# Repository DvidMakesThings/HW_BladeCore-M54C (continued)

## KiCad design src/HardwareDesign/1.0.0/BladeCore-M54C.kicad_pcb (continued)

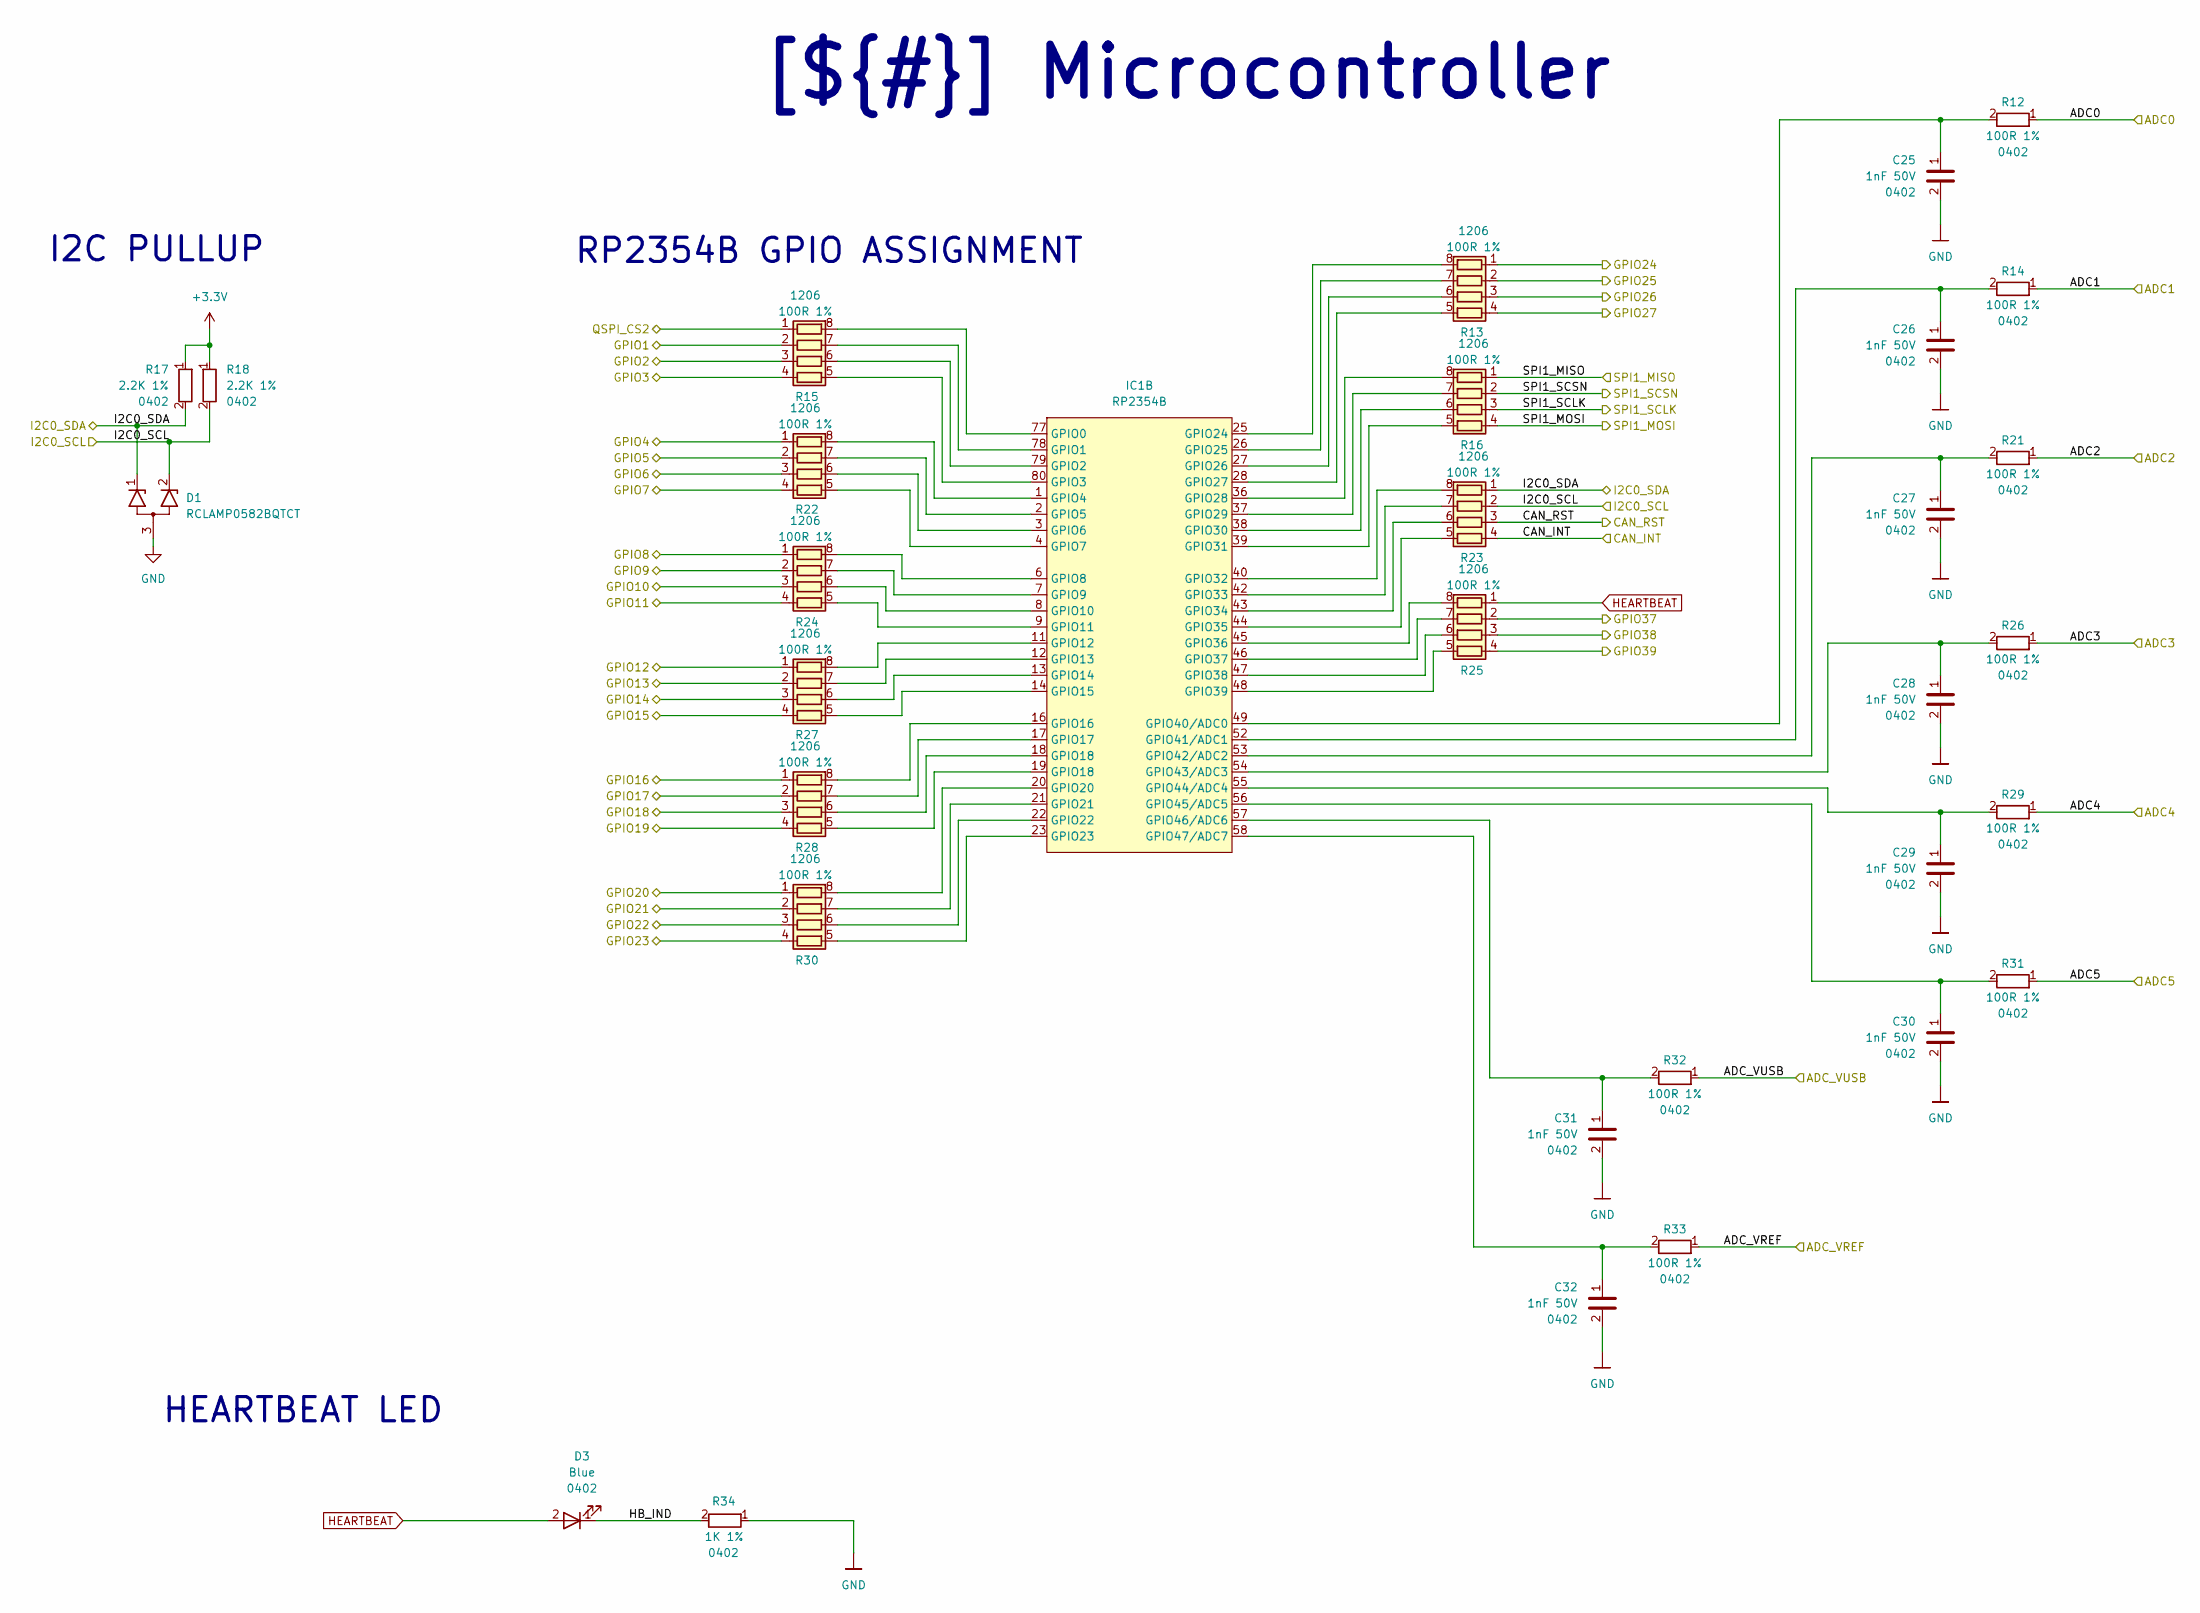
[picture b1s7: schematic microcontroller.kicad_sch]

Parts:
C25, C26, C27, C28, C29, C30, C31, C32: 1nF 50V; C_0402_1005Metric; LCSC_PART C14442
D1: RCLAMP0582BQTCT; SOT-416; MPN RCLAMP0582BQTCT; LCSC_PART C841193
D3: Blue; LED_0402_1005Metric; MPN XL-1005UBC; LCSC_PART C22355736
IC1: RP2354B; QFN80_10x10; MPN RP2354B; LCSC_PART C39843328
R12, R14, R21, R26, R29, R31, R32, R33: 100R 1%; R_0402_1005Metric; LCSC_PART C25076
R13, R15, R16, R22, R23, R24, R25, R27, R28, R30: 100R 1%; R_Array_Convex_4x0603; MPN YC164-FR-07100RL; LCSC_PART C136838
R17, R18: 2.2K 1%; R_0402_1005Metric; LCSC_PART C25879
R34: 1K 1%; R_0402_1005Metric; LCSC_PART C11702

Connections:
+3.3V: R17.1, R18.1; also elsewhere on the board
/Project Architecture/ADC0: R12.1; also elsewhere on the board
/Project Architecture/ADC1: R14.1; also elsewhere on the board
/Project Architecture/ADC2: R21.1; also elsewhere on the board
/Project Architecture/ADC3: R26.1; also elsewhere on the board
/Project Architecture/ADC4: R29.1; also elsewhere on the board
/Project Architecture/ADC5: R31.1; also elsewhere on the board
/Project Architecture/GPIO0: R15.1 (R11); also elsewhere on the board
/Project Architecture/GPIO1: R15.2 (R12); also elsewhere on the board
/Project Architecture/GPIO2: R15.3 (R13); also elsewhere on the board
/Project Architecture/GPIO3: R15.4 (R14); also elsewhere on the board
/Project Architecture/GPIO4: R22.1 (R11); also elsewhere on the board
/Project Architecture/GPIO5: R22.2 (R12); also elsewhere on the board
/Project Architecture/GPIO6: R22.3 (R13); also elsewhere on the board
/Project Architecture/GPIO7: R22.4 (R14); also elsewhere on the board
/Project Architecture/GPIO8: R24.1 (R11); also elsewhere on the board
/Project Architecture/GPIO9: R24.2 (R12); also elsewhere on the board
/Project Architecture/GPIO10: R24.3 (R13); also elsewhere on the board
/Project Architecture/GPIO11: R24.4 (R14); also elsewhere on the board
/Project Architecture/GPIO12: R27.1 (R11); also elsewhere on the board
/Project Architecture/GPIO13: R27.2 (R12); also elsewhere on the board
/Project Architecture/GPIO14: R27.3 (R13); also elsewhere on the board
/Project Architecture/GPIO15: R27.4 (R14); also elsewhere on the board
/Project Architecture/GPIO16: R28.1 (R11); also elsewhere on the board
/Project Architecture/GPIO17: R28.2 (R12); also elsewhere on the board
/Project Architecture/GPIO18: R28.3 (R13); also elsewhere on the board
/Project Architecture/GPIO19: R28.4 (R14); also elsewhere on the board
/Project Architecture/GPIO20: R30.1 (R11); also elsewhere on the board
/Project Architecture/GPIO21: R30.2 (R12); also elsewhere on the board
/Project Architecture/GPIO22: R30.3 (R13); also elsewhere on the board
/Project Architecture/GPIO23: R30.4 (R14); also elsewhere on the board
/Project Architecture/GPIO24: R13.1 (R11); also elsewhere on the board
/Project Architecture/GPIO25: R13.2 (R12); also elsewhere on the board
/Project Architecture/GPIO26: R13.3 (R13); also elsewhere on the board
/Project Architecture/GPIO27: R13.4 (R14); also elsewhere on the board
/Project Architecture/Microcontroller Peripherals/ADC_VREF: R33.1; also elsewhere on the board
/Project Architecture/Microcontroller Peripherals/I2C0_SCL: D1.2 (K2), R18.2, R23.2 (R12); also elsewhere on the board
/Project Architecture/Microcontroller Peripherals/I2C0_SDA: D1.1 (K1), R17.2, R23.1 (R11); also elsewhere on the board
/Project Architecture/Microcontroller/ADC_VUSB: R32.1; also elsewhere on the board
/Project Architecture/Microcontroller/CAN_INT: R23.4 (R14); also elsewhere on the board
/Project Architecture/Microcontroller/CAN_RST: R23.3 (R13); also elsewhere on the board
/Project Architecture/Microcontroller/GPIO37: R25.2 (R12); also elsewhere on the board
/Project Architecture/Microcontroller/GPIO38: R25.3 (R13); also elsewhere on the board
/Project Architecture/Microcontroller/GPIO39: R25.4 (R14); also elsewhere on the board
/Project Architecture/Microcontroller/HB_IND: D3.1, R34.2
/Project Architecture/Microcontroller/SPI1_MISO: R16.1 (R11); also elsewhere on the board
/Project Architecture/Microcontroller/SPI1_MOSI: R16.4 (R14); also elsewhere on the board
/Project Architecture/Microcontroller/SPI1_SCLK: R16.3 (R13); also elsewhere on the board
/Project Architecture/Microcontroller/SPI1_SCSN: R16.2 (R12); also elsewhere on the board
GND: C25.2, C26.2, C27.2, C28.2, C29.2, C30.2, C31.2, C32.2, D1.3 (A), R34.1; also elsewhere on the board
HEARTBEAT: D3.2, R25.1 (R11)
unnamed: IC1.77 (GPIO0), R15.8 (R12)
unnamed: IC1.78 (GPIO1), R15.7 (R22)
unnamed: IC1.79 (GPIO2), R15.6 (R23)
unnamed: IC1.80 (GPIO3), R15.5 (R24)
unnamed: IC1.1 (GPIO4), R22.8 (R12)
unnamed: IC1.2 (GPIO5), R22.7 (R22)
unnamed: IC1.3 (GPIO6), R22.6 (R23)
unnamed: IC1.4 (GPIO7), R22.5 (R24)
unnamed: IC1.6 (GPIO8), R24.8 (R12)
unnamed: IC1.7 (GPIO9), R24.7 (R22)
unnamed: IC1.8 (GPIO10), R24.6 (R23)
unnamed: IC1.9 (GPIO11), R24.5 (R24)
unnamed: IC1.11 (GPIO12), R27.8 (R12)
unnamed: IC1.12 (GPIO13), R27.7 (R22)
unnamed: IC1.13 (GPIO14), R27.6 (R23)
unnamed: IC1.14 (GPIO15), R27.5 (R24)
unnamed: IC1.16 (GPIO16), R28.8 (R12)
unnamed: IC1.17 (GPIO17), R28.7 (R22)
unnamed: IC1.20 (GPIO20), R30.8 (R12)
unnamed: IC1.21 (GPIO21), R30.7 (R22)
unnamed: IC1.22 (GPIO22), R30.6 (R23)
unnamed: IC1.23 (GPIO23), R30.5 (R24)
unnamed: IC1.25 (GPIO24), R13.8 (R12)
unnamed: IC1.26 (GPIO25), R13.7 (R22)
unnamed: IC1.27 (GPIO26), R13.6 (R23)
unnamed: IC1.28 (GPIO27), R13.5 (R24)
unnamed: IC1.36 (GPIO28), R16.8 (R12)
unnamed: IC1.37 (GPIO29), R16.7 (R22)
unnamed: IC1.38 (GPIO30), R16.6 (R23)
unnamed: IC1.39 (GPIO31), R16.5 (R24)
unnamed: IC1.40 (GPIO32), R23.8 (R12)
unnamed: IC1.42 (GPIO33), R23.7 (R22)
unnamed: IC1.43 (GPIO34), R23.6 (R23)
unnamed: IC1.44 (GPIO35), R23.5 (R24)
unnamed: IC1.45 (GPIO36), R25.8 (R12)
unnamed: IC1.46 (GPIO37), R25.7 (R22)
unnamed: IC1.47 (GPIO38), R25.6 (R23)
unnamed: IC1.48 (GPIO39), R25.5 (R24)
unnamed: C25.1, IC1.49 (GPIO40/ADC0), R12.2
unnamed: C26.1, IC1.52 (GPIO41/ADC1), R14.2
unnamed: C27.1, IC1.53 (GPIO42/ADC2), R21.2
unnamed: C28.1, IC1.54 (GPIO43/ADC3), R26.2
unnamed: C29.1, IC1.55 (GPIO44/ADC4), R29.2
unnamed: C30.1, IC1.56 (GPIO45/ADC5), R31.2
unnamed: C31.1, IC1.57 (GPIO46/ADC6), R32.2
unnamed: C32.1, IC1.58 (GPIO47/ADC7), R33.2
unnamed: IC1.18 (GPIO18), R28.6 (R23)
unnamed: IC1.19 (GPIO18), R28.5 (R24)

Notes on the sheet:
I2C PULLUP
HEARTBEAT LED
RP2354B GPIO ASSIGNMENT
[${#}] ${TITLE}

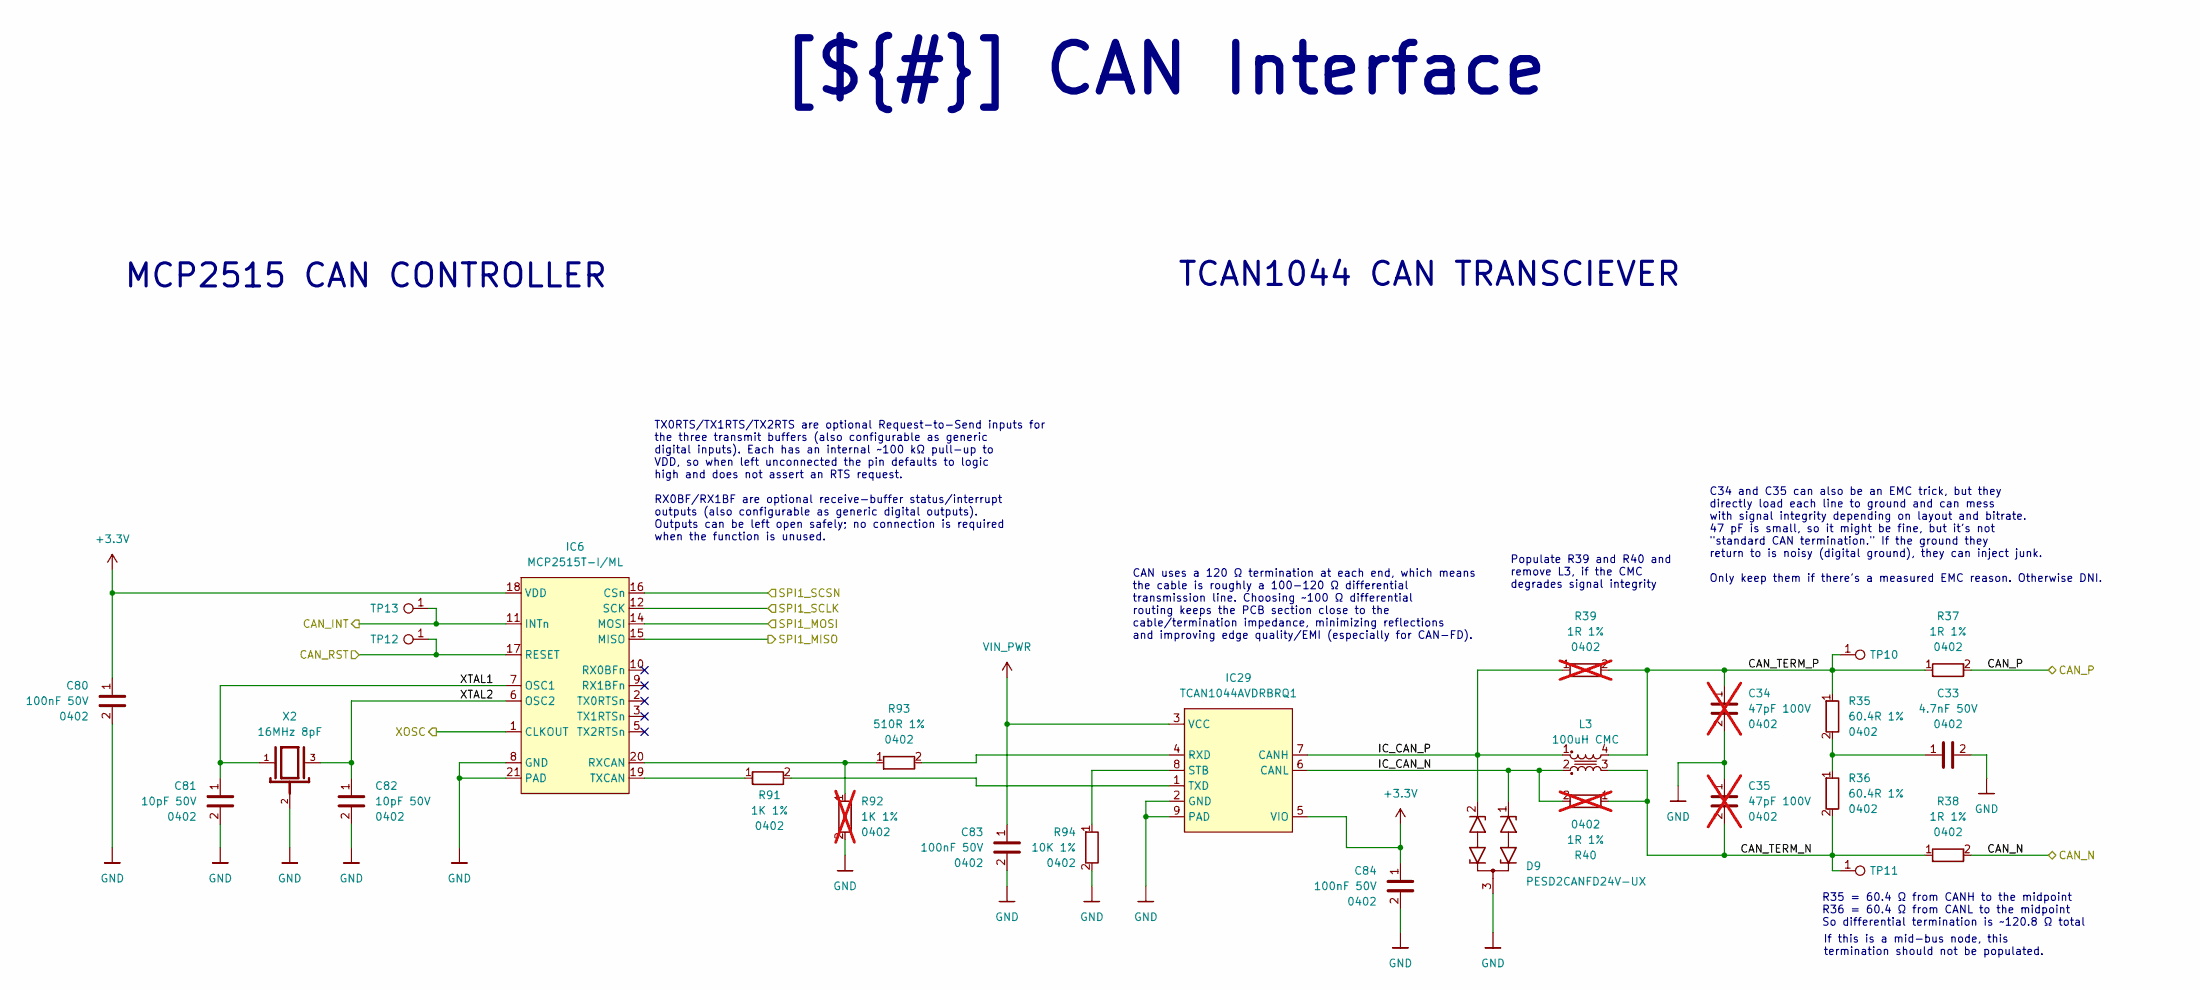
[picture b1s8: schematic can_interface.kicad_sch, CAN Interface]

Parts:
C33: 4.7nF 50V; C_0402_1005Metric; LCSC_PART C1538
C34, C35: 47pF 100V; C_0402_1005Metric; LCSC_PART C5358466; not fitted
C80, C83, C84: 100nF 50V; C_0402_1005Metric; LCSC_PART C307331
C81, C82: 10pF 50V; C_0402_1005Metric; LCSC_PART C466222
D9: PESD2CANFD24V-UX; SOT-323_SC-70; MPN PESD2CANFD24V-UX; LCSC_PART C46970732
IC6: MCP2515T-I/ML; QFN-20-1EP_4x4mm_P0.5mm_EP2.7x2.7mm; MPN MCP2515T-I/ML; LCSC_PART C96140
IC29: TCAN1044AVDRBRQ1; HVSON-8-1EP_3x3mm_P0.65mm_EP1.6x2.4mm; MPN TCAN1044AVDRBRQ1; LCSC_PART C3234119
L3: 100uH CMC; ACT1210D-101-2P-TL00; MPN ACT1210D-101-2P-TL00; LCSC_PART C3039743
R35, R36: 60.4R 1%; R_0402_1005Metric; MPN RC0402FR-0760R4L; LCSC_PART C137954
R37, R38: 1R 1%; R_0402_1005Metric; MPN RC0402FR-071RL; LCSC_PART C185446
R39, R40: 1R 1%; R_0402_1005Metric; MPN RC0402FR-071RL; LCSC_PART C185446; not fitted
R91: 1K 1%; R_0402_1005Metric; LCSC_PART C11702
R92: 1K 1%; R_0402_1005Metric; LCSC_PART C11702; not fitted
R93: 510R 1%; R_0402_1005Metric; MPN 0402WGF5100TCE; LCSC_PART C25123
R94: 10K 1%; R_0402_1005Metric; LCSC_PART C25744
TP10, TP11, TP12, TP13: TestPoint_0.6mm
X2: 16MHz 8pF; Crystal_SMD_2016-4Pin_2.0x1.6mm; MPN CS07826-16M; LCSC_PART C2965577

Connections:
+3.3V: C80.1, C84.1, IC6.18 (VDD), IC29.5 (VIO); also elsewhere on the board
/Project Architecture/CAN Interface/CAN_TERM_N: C35.2, L3.3, R36.2, R38.1, R40.1, TP11.1
/Project Architecture/CAN Interface/CAN_TERM_P: C34.1, L3.4, R35.1, R37.1, R39.2, TP10.1
/Project Architecture/CAN Interface/IC_CAN_N: D9.1 (K1), IC29.6 (CANL), L3.2, R40.2
/Project Architecture/CAN Interface/IC_CAN_P: D9.2 (K2), IC29.7 (CANH), L3.1, R39.1
/Project Architecture/CAN Interface/XOSC: IC6.1 (CLKOUT)
/Project Architecture/CAN Interface/XTAL1: C81.1, IC6.7 (OSC1), X2.1
/Project Architecture/CAN Interface/XTAL2: C82.1, IC6.6 (OSC2), X2.3
/Project Architecture/CAN_N: R38.2; also elsewhere on the board
/Project Architecture/CAN_P: R37.2; also elsewhere on the board
/Project Architecture/Microcontroller/CAN_INT: IC6.11 (INTn), TP13.1; also elsewhere on the board
/Project Architecture/Microcontroller/CAN_RST: IC6.17 (RESET), TP12.1; also elsewhere on the board
/Project Architecture/Microcontroller/SPI1_MISO: IC6.15 (MISO); also elsewhere on the board
/Project Architecture/Microcontroller/SPI1_MOSI: IC6.14 (MOSI); also elsewhere on the board
/Project Architecture/Microcontroller/SPI1_SCLK: IC6.12 (SCK); also elsewhere on the board
/Project Architecture/Microcontroller/SPI1_SCSN: IC6.16 (CSn); also elsewhere on the board
GND: C33.2, C34.2, C35.1, C80.2, C81.2, C82.2, C83.2, C84.2, D9.3 (A), IC6.8 (GND), IC6.21 (PAD), IC29.2 (GND), IC29.9 (PAD), R92.2, R94.2, X2.2; also elsewhere on the board
unnamed: C33.1, R35.2, R36.1
unnamed: IC6.20 (RXCAN), R92.1, R93.1
unnamed: IC6.19 (TXCAN), R91.1
unnamed: IC29.4 (RXD), R93.2
unnamed: IC29.8 (STB), R94.1
unnamed: IC29.1 (TXD), R91.2
VIN_PWR: C83.1, IC29.3 (VCC); also elsewhere on the board

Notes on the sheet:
MCP2515 CAN CONTROLLER
Populate R39 and R40 and remove L3, if the CMC degrades signal integrity
R35 = 60.4 Ω from CANH to the midpoint R36 = 60.4 Ω from CANL to the midpoint So differential termination is ~120.8 Ω total
TX0RTS/TX1RTS/TX2RTS are optional Request-to-Send inputs for the three transmit buffers (also configurable as generic digital inputs). Each has an internal ~100 kΩ pull-up to VDD, so when left unconnected the pin defaults to logic high and does not assert an RTS request. RX0BF/RX1BF are optional re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
CAN uses a 120 Ω termination at each end, which means the cable is roughly a 100-120 Ω differential transmission line. Choosing ~100 Ω differential routing keeps the PCB section close to the cable/termination impedance, minimizing reflections and improving edge quality/EMI (especially for CAN-FD).
C34 and C35 can also be an EMC trick, but they directly load each line to ground and can mess with signal integrity depending on layout and bitrate. 47 pF is small, so it might be fine, but it's not "standard CAN termination." If the ground they return to is noisy (digital ground), they can inject 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
If this is a mid-bus node, this termination should not be populated.
TCAN1044 CAN TRANSCIEVER
[${#}] ${TITLE}

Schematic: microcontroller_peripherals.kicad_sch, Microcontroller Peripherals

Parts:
C1, C2, C3, C4, C5, C7, C8, C9, C10, C13, C14, C15, C17, C18, C19, C21, C23: 100nF 50V; C_0402_1005Metric; LCSC_PART C307331
C6, C16: 4.7uF 25V; C_0402_1005Metric; LCSC_PART C22367824
C11, C12: 10pF 50V; C_0402_1005Metric; LCSC_PART C466222
C20, C22, C24: 4.7uF 10V; C_0402_1005Metric; LCSC_PART C368809
IC1: RP2354B; QFN80_10x10; MPN RP2354B; LCSC_PART C39843328
IC2: AT24C256C-XHL-T; TSSOP-8; MPN AT24C256C-XHL-T; LCSC_PART C33035
IC3: W25Q128JVPIQ; WSON8_6x5; MPN W25Q128JVPIQ; LCSC_PART C190862
IC4: MCP6001RT; SOT-23-5; MPN MCP6001RT-I/OT; LCSC_PART C154973
IC5: LM4040B30FTA; SOT-23; MPN LM4040B30FTA; LCSC_PART C460604
J2: SM03B-SRSS-TB; JST_SM03B-SRSS-TB_LF__SN_; MPN SM03B-SRSS-TB; LCSC_PART C160403
L1: 3.3uH 2.8A; 0805; MPN AOTA-B201610S3R3-101-T; LCSC_PART C42411119
R1, R8: 4.7K 1%; R_0402_1005Metric; LCSC_PART C25900
R2, R3, R4: 33R 1%; R_0402_1005Metric; LCSC_PART C25105
R5: 1K 1%; R_0402_1005Metric; LCSC_PART C11702
R6: 1K 1%; R_0402_1005Metric; LCSC_PART C11702; not fitted
R7: 27R 1%; R_0402_1005Metric; LCSC_PART C138021
R9: 27R 1%; R_0402_1005Metric; LCSC_PART C138021; not fitted
R10, R11: 10K 1%; R_0402_1005Metric; LCSC_PART C25744
SW1, SW2: B3U-1000P; SW_B3U-1000P; MPN B3U-1000P; LCSC_PART C231329
TP14, TP15, TP16, TP17: TestPoint_0.6mm
X1: 12MHz 10pF; X3225; MPN SX3B12.000F1010F30; LCSC_PART C2901649

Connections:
+1V1: C13.1, C14.1, C15.1, C16.1, IC1.10 (DVDD1), IC1.32 (DVDD2), IC1.51 (DVDD3), IC1.65 (VREF_FB), L1.1, TP17.1
+3.3V: C1.1, C2.1, C3.1, C4.1, C5.1, C7.1, C8.1, C9.1, C10.1, C17.1, C18.1, C20.1, IC1.5 (IOVDD1), IC1.15 (IOVDD2), IC1.24 (IOVDD3), IC1.29 (IOVDD4), IC1.41 (IOVDD5), IC1.50 (IOVDD6), IC1.60 (IOVDD7), IC1.64 (VREG_IN), IC1.68 (USB_OTP_VDD), IC1.69 (QSPI_IOVDD), IC1.76 (IOVDD8), IC2.8 (VCC), IC3.8 (VCC), R1.1, R2.1, R6.1, R7.2, R8.1, R9.2; also elsewhere on the board
/Project Architecture/Microcontroller Peripherals/ADC_VREF: R10.2, R11.1, TP14.1; also elsewhere on the board
/Project Architecture/Microcontroller Peripherals/I2C0_SCL: IC2.6 (SCL); also elsewhere on the board
/Project Architecture/Microcontroller Peripherals/I2C0_SDA: IC2.5 (SDA); also elsewhere on the board
/Project Architecture/Microcontroller Peripherals/RP_D+: IC1.67 (USB_DP), R4.2
/Project Architecture/Microcontroller Peripherals/RP_D-: IC1.66 (USB_DM), R3.1
/Project Architecture/Microcontroller Peripherals/SWCLK: IC1.33 (SWCLK), J2.1 (SWCLK)
/Project Architecture/Microcontroller Peripherals/SWDIO: IC1.34 (SWDIO), J2.3 (SWDAT)
/Project Architecture/Microcontroller Peripherals/VREF_IN: C21.1, C22.1, IC4.3 (+), IC5.1 (K), R8.2, TP16.1
/Project Architecture/Microcontroller Peripherals/VREG_AVDD: C6.1, IC1.61 (VREG_AVDD), R2.2
/Project Architecture/Microcontroller Peripherals/VREG_LX: IC1.63 (VREG_LC), L1.2
/Project Architecture/Microcontroller Peripherals/XIN: C12.1, IC1.30 (XIN), X1.3
/Project Architecture/Microcontroller Peripherals/XO: C11.1, R5.2, X1.1
/Project Architecture/Microcontroller Peripherals/XOUT: IC1.31 (XOUT), R5.1
/Project Architecture/USB Interface and Power/USB_RP_D+: R4.1; also elsewhere on the board
/Project Architecture/USB Interface and Power/USB_RP_D-: R3.2; also elsewhere on the board
GND: C1.2, C2.2, C3.2, C4.2, C5.2, C6.2, C7.2, C8.2, C9.2, C10.2, C11.2, C12.2, C13.2, C14.2, C15.2, C16.2, C17.2, C18.2, C19.2, C20.2, C21.2, C22.2, C23.2, C24.2, IC1.62 (VREG_PGND), IC1.81 (GND), IC2.1 (A0), IC2.2 (A1), IC2.3 (A2), IC2.4 (GND), IC2.7 (WP), IC3.4 (GND), IC3.9 (PAD), IC4.5 (V-), IC5.2 (A), J2.2 (GND), J2.S1 (SHIELD), J2.S2 (SHIELD), R11.2, SW1.2, SW2.2, X1.2; also elsewhere on the board
unnamed: C19.1, IC4.2 (V+), R7.1
QSPI_SCLK: IC1.71 (QSPI_SCLK), IC3.6 (CLK)
QSPI_SD0: IC1.72 (QSPI_SD0), IC3.5 (DI(IO0))
QSPI_SD1: IC1.74 (QSPI_SD1), IC3.2 (DO(IO1))
QSPI_SD2: IC1.73 (QSPI_SD2), IC3.3 (nWP(IO2))
QSPI_SD3: IC1.70 (QSPI_SD3), IC3.7 (nRST(IO3))
QSPI_SS: IC1.75 (QSPI_SS), IC3.1 (nCS), R6.2, SW1.1
RESET: IC1.35 (RUN), R1.2, SW2.1
VREF_OUT: C23.1, C24.1, IC1.59 (ADC_AVDD), IC4.1, IC4.4 (-), R9.1, R10.1, TP15.1

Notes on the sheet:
EXTERNAL EEPROM
PUSHBUTTONS
EXTERNAL FLASH
RP2354B MICROCONTROLLER
HW Design Guide: RC filter of 33Ω and 4.7μF is adequate
HW Design Guide: recommended to use 100nF capacitor per power pin
3.0V ADC VOLTAGE REFERENCE
12MHz 10pF -> Assuming 5pF parasitics Csum = 10pF - 5pF = 5pF C1 = C2 = 5pF x 2 = 10pF
[${#}] ${TITLE}

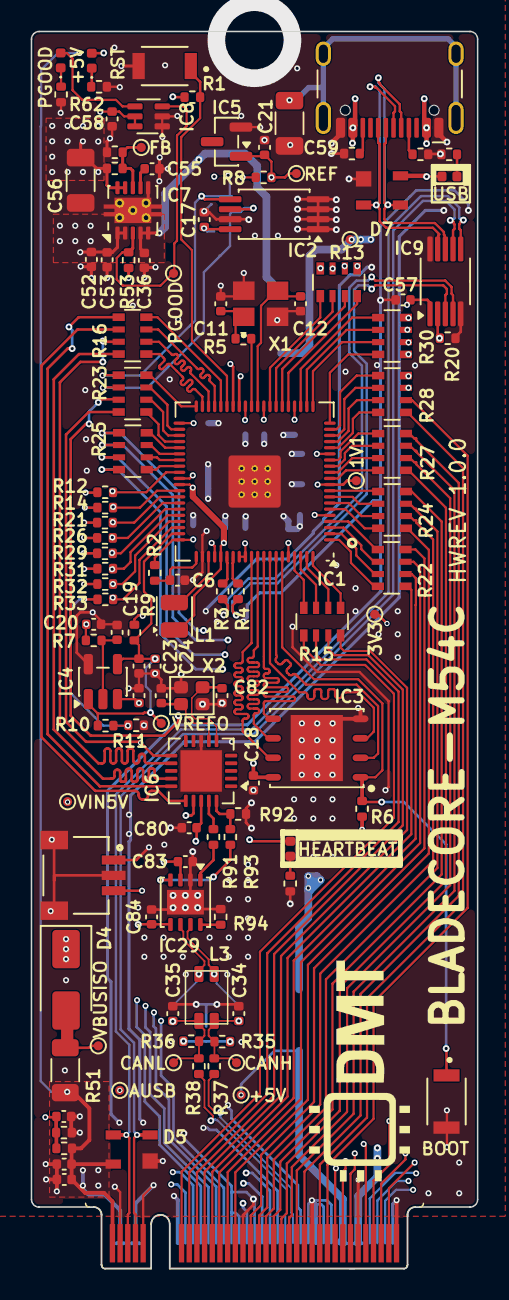
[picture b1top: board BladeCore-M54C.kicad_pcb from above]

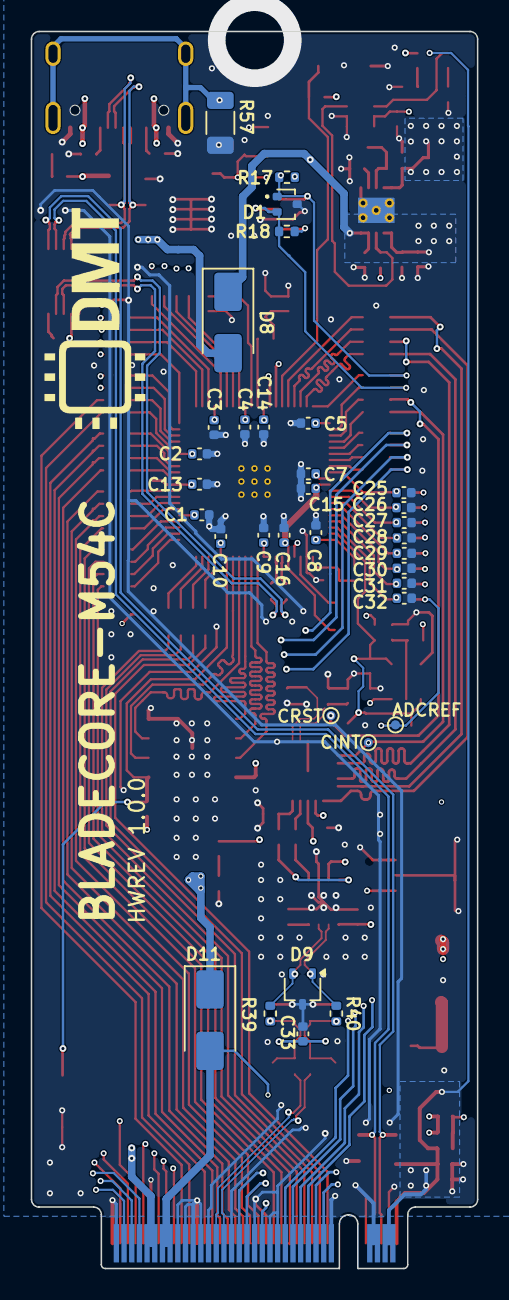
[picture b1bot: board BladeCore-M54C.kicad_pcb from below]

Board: 6 copper layers, 29.0 x 80.6 mm, 152 parts (34 on the bottom side), 154 nets.

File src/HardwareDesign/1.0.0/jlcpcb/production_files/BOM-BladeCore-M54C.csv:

Comment,Designator,Footprint,LCSC,Quantity
0R 1%,R51,R_1206_3216Metric,C205296,1
100R 1%,"R13,R15,R16,R22,R23,R24,R25,R27,R28,R30",R_Array_Convex_4x0603,C136838,10
100R 1%,"R12,R14,R21,R26,R29,R31,R32,R33",R_0402_1005Metric,C25076,8
100nF 50V,"C1,C10,C13,C14,C15,C17,C18,C19,C2,C21,C23,C3,C4,C5,C51,C52,C57,C58,C7,C8,C80,C83,C84,C9",C_0402_1005Metric,C307331,24
100uH CMC,L3,ACT1210D-101-2P-TL00,C3039743,1
10K 1%,"R10,R11,R53,R94",R_0402_1005Metric,C25744,4
10pF 50V,"C11,C12,C81,C82",C_0402_1005Metric,C466222,4
10uF 50V,C56,C_1206_3216Metric,C13585,1
12MHz 10pF,X1,X3225,C2901649,1
16MHz 8pF,X2,Crystal_SMD_2016-4Pin_2.0x1.6mm,C2965577,1
1K 1%,"R34,R41,R5,R60,R62,R91",R_0402_1005Metric,C11702,6
1M 1%,R57,R_1206_3216Metric,C17927,1
1R 1%,"R37,R38",R_0402_1005Metric,C185446,2
1nF 2kV,C59,C_1206_3216Metric,C173242,1
1nF 50V,"C25,C26,C27,C28,C29,C30,C31,C32",C_0402_1005Metric,C14442,8
1uF 50V,C53,C_0402_1005Metric,C1518208,1
2.2K 1%,"R17,R18",R_0402_1005Metric,C25879,2
2.2nF 50V,C55,C_0402_1005Metric,C106861,1
2.4K 1%,R59,R_0402_1005Metric,C25882,1
27R 1%,R7,R_0402_1005Metric,C138021,1
3.3uH 2.8A,L1,0805,C42411119,1
33R 1%,"R2,R3,R4",R_0402_1005Metric,C25105,3
4.7K 1%,"R1,R8",R_0402_1005Metric,C25900,2
4.7nF 50V,C33,C_0402_1005Metric,C1538,1
4.7uF 10V,"C20,C22,C24",C_0402_1005Metric,C368809,3
4.7uF 25V,"C16,C36,C49,C50,C6",C_0402_1005Metric,C22367824,5
5.1K 1%,"R19,R20,R52,R55,R56",R_0402_1005Metric,C25905,5
510R 1%,R93,R_0402_1005Metric,C25123,1
60.4R 1%,"R35,R36",R_0402_1005Metric,C137954,2
7.5K 1%,R54,R_0402_1005Metric,C25918,1
AT24C256C-XHL-T,IC2,TSSOP-8,C33035,1
B3U-1000P,"SW1,SW2",SW_B3U-1000P,C231329,2
Blue,D3,LED_0402_1005Metric,C22355736,1
FSUSB42MUX,IC9,MSOP-10_3x3mm_P0.5mm,C11355,1
Green,"D10,D2,D6",LED_0402_1005Metric,C965793,3
LM4040B30FTA,IC5,SOT-23,C460604,1
MCP2515T-I/ML,IC6,QFN-20-1EP_4x4mm_P0.5mm_EP2.7x2.7mm,C96140,1
MCP6001RT,IC4,SOT-23-5,C154973,1
PESD2CANFD24V-UX,D9,SOT-323_SC-70,C46970732,1
RCLAMP0582BQTCT,D1,SOT-416,C841193,1
RP2354B,IC1,QFN80_10x10,C39843328,1
SM03B-SRSS-TB,J2,JST_SM03B-SRSS-TB_LF__SN_,C160403,1
SN74LVC1G97QDCKRQ1,IC8,SOT-363_SC-70-6,C179911,1
SP0503BAHTG,"D5,D7",SOT143,C3040626,2
TCAN1044AVDRBRQ1,IC29,HVSON-8-1EP_3x3mm_P0.65mm_EP1.6x2.4mm,C3234119,1
TPS74801DRCT,IC7,VSON-10-1EP_3x3mm_P0.5mm_EP1.65x2.4mm_ThermalVias,C882845,1
USB-TYPE-C-018,J3,USB_C_Receptacle_HCTL_HC-TYPE-C-16P-01A,C2927038,1
W25Q128JVPIQ,IC3,WSON8_6x5,C190862,1
SS13,D4,D_SMA,,1
~,TP6,TestPoint_0.6mm,,1
~,TP1,TestPoint_0.6mm,,1
~,TP8,TestPoint_0.6mm,,1
~,TP10,TestPoint_0.6mm,,1
~,TP7,TestPoint_0.6mm,,1
~,TP2,TestPoint_0.6mm,,1
~,TP3,TestPoint_0.6mm,,1
~,TP4,TestPoint_0.6mm,,1
~,TP15,TestPoint_0.6mm,,1
~,TP16,TestPoint_0.6mm,,1
~,TP17,TestPoint_0.6mm,,1
~,TP11,TestPoint_0.6mm,,1
~,TP5,TestPoint_0.6mm,,1
~,TP12,TestPoint_0.6mm,,1
~,TP13,TestPoint_0.6mm,,1
SS13,D11,D_SMA,,1
~,TP14,TestPoint_0.6mm,,1
SS13,D8,D_SMA,,1

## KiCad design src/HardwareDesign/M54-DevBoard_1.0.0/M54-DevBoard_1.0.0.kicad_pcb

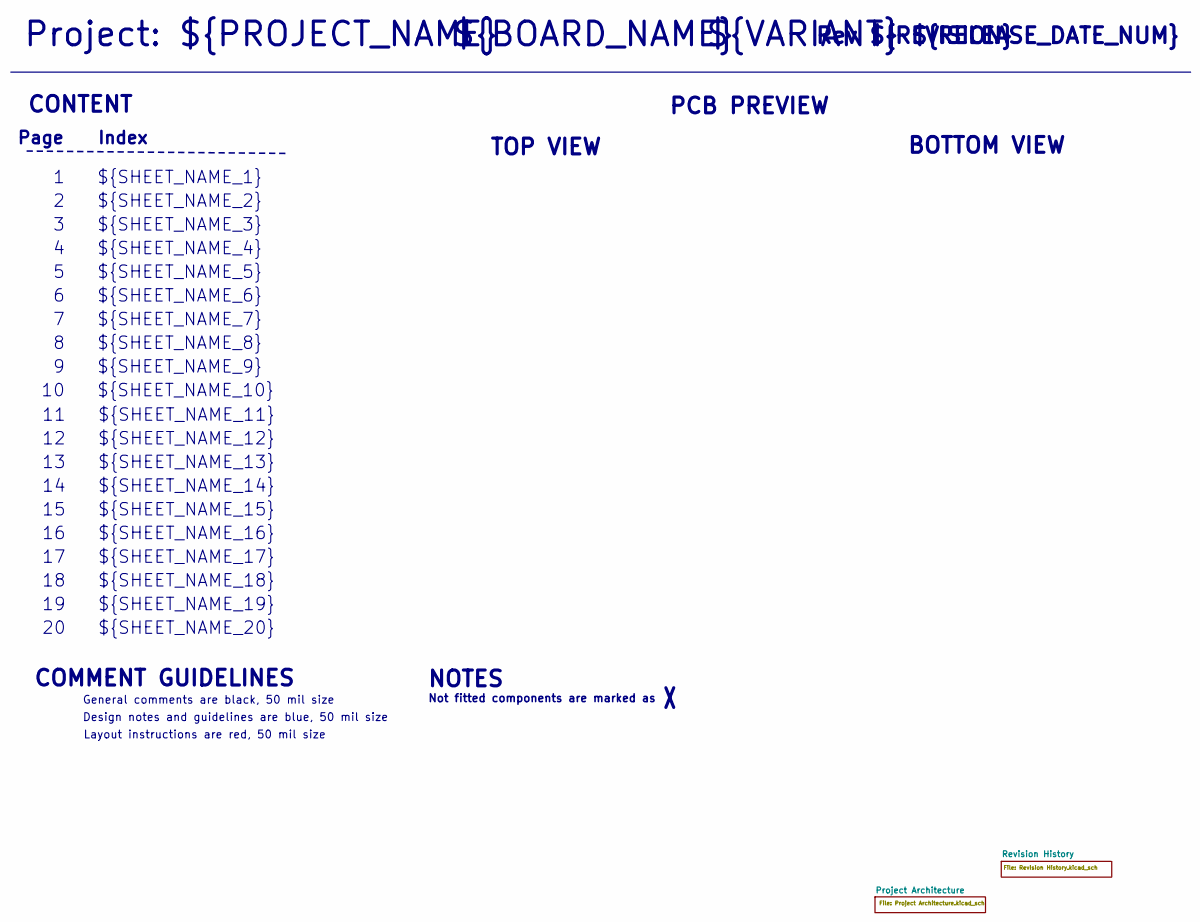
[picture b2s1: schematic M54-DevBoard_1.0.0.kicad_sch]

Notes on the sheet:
${SHEET_NAME_12}
${SHEET_NAME_8}
${SHEET_NAME_2}
${SHEET_NAME_5}
${SHEET_NAME_20}
Page
PCB PREVIEW
${RELEASE_DATE_NUM}
CONTENT
${SHEET_NAME_11}
${SHEET_NAME_6}
Rev ${REVISION}
${SHEET_NAME_15}
BOTTOM VIEW
${SHEET_NAME_14}
${SHEET_NAME_17}
${SHEET_NAME_18}
${SHEET_NAME_7}
Not fitted components are marked as
Project: ${PROJECT_NAME}
NOTES
Design notes and guidelines are blue, 50 mil size
${SHEET_NAME_1}
${SHEET_NAME_9}
${BOARD_NAME}
General comments are black, 50 mil size
${SHEET_NAME_16}
${SHEET_NAME_3}
${VARIANT}
${SHEET_NAME_19}
TOP VIEW
${SHEET_NAME_10}
Index
${SHEET_NAME_13}
${SHEET_NAME_4}
COMMENT GUIDELINES
Layout instructions are red, 50 mil size

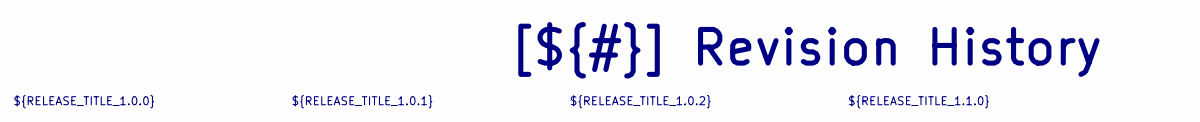
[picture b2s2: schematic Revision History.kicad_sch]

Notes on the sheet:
[${#}] ${TITLE}
${RELEASE_TITLE_1.0.2}
${RELEASE_TITLE_1.0.0}
${RELEASE_TITLE_1.0.1}
${RELEASE_TITLE_1.1.0}

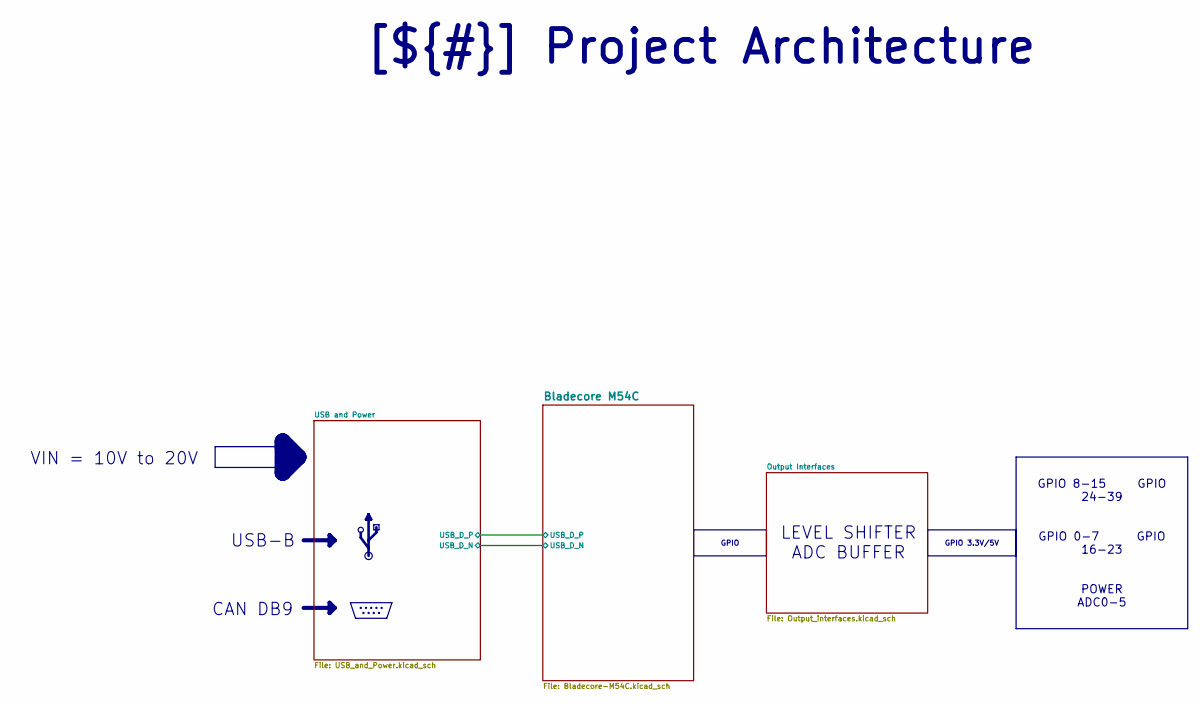
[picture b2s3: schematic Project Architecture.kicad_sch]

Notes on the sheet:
VIN = 10V to 20V
LEVEL SHIFTER ADC BUFFER
CAN DB9
USB-B
GPIO 8-15 GPIO 24-39 GPIO 0-7 GPIO 16-23 POWER ADC0-5
GPIO 3.3V/5V
GPIO
[${#}] ${TITLE}

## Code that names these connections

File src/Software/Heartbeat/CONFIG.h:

/*
 * CONFIG.h - BladeCore-M54C Board Pin Configuration
 *
 * Pin assignments derived from the BladeCore-M54C hardware schematics (v1.0.0).
 * MCU: RP2354B (QFN-80)
 */

#ifndef CONFIG_H
#define CONFIG_H

/* -------------------------------------------------------------------------- */
/*  MCP2515 CAN Controller (SPI1)                                             */
/* -------------------------------------------------------------------------- */
#define PIN_CAN_MISO 28 /* SPI1 RX  - MCP2515 SO             */
#define PIN_CAN_CS 29   /* SPI1 CSn - MCP2515 CS (active low)*/
#define PIN_CAN_SCK 30  /* SPI1 SCK - MCP2515 SCK            */
#define PIN_CAN_MOSI 31 /* SPI1 TX  - MCP2515 SI             */

/* -------------------------------------------------------------------------- */
/*  I2C0 - Onboard EEPROM (AT24C256) + M.2 connector                         */
/* -------------------------------------------------------------------------- */
#define PIN_I2C0_SDA 32 /* I2C0 data  (4.7K pull-up)         */
#define PIN_I2C0_SCL 33 /* I2C0 clock (4.7K pull-up)         */

/* -------------------------------------------------------------------------- */
/*  MCP2515 CAN Control                                                       */
/* -------------------------------------------------------------------------- */
#define PIN_CAN_RST 34 /* MCP2515 hardware reset (active low)*/
#define PIN_CAN_INT 35 /* MCP2515 interrupt (active low)    */

/* -------------------------------------------------------------------------- */
/*  Onboard Heartbeat LED                                                     */
/* -------------------------------------------------------------------------- */
#define PIN_HEARTBEAT 36 /* Blue LED, 100R series resistor    */

/* -------------------------------------------------------------------------- */
/*  ADC - Onboard                                                             */
/* -------------------------------------------------------------------------- */
#define PIN_ADC_VUSB 46 /* GPIO46/ADC6 - USB VBUS sense (5.1K-5.1K divider) */
#define PIN_ADC_VREF 47 /* GPIO47/ADC7 - 3.00V 0.1% ref (10K-10K divider)   */

/* -------------------------------------------------------------------------- */
/*  Unused GPIOs - M.2 Connector (directly access through M.2 edge connector) */
/* -------------------------------------------------------------------------- */
/*  Left side (odd pins)                                                      */
// #define PIN_GPIO0             0       /* M.2 pin 57             */
// #define PIN_GPIO1             1       /* M.2 pin 55             */
// #define PIN_GPIO2             2       /* M.2 pin 53             */
// #define PIN_GPIO3             3       /* M.2 pin 51             */
// #define PIN_GPIO4             4       /* M.2 pin 49             */
// #define PIN_GPIO5             5       /* M.2 pin 47             */
// #define PIN_GPIO6             6       /* M.2 pin 45             */
// #define PIN_GPIO7             7       /* M.2 pin 43             */
// #define PIN_GPIO8             8       /* M.2 pin 39             */
// #define PIN_GPIO9             9       /* M.2 pin 37             */
// #define PIN_GPIO10            10      /* M.2 pin 35             */
// #define PIN_GPIO11            11      /* M.2 pin 33             */
// #define PIN_GPIO12            12      /* M.2 pin 31             */
// #define PIN_GPIO13            13      /* M.2 pin 29             */
// #define PIN_GPIO14            14      /* M.2 pin 27             */
// #define PIN_GPIO15            15      /* M.2 pin 25             */
// #define PIN_GPIO16            16      /* M.2 pin 21             */
// #define PIN_GPIO17            17      /* M.2 pin 19             */
// #define PIN_GPIO18            18      /* M.2 pin 17             */
// #define PIN_GPIO19            19      /* M.2 pin 15             */
// #define PIN_GPIO20            20      /* M.2 pin 13             */
// #define PIN_GPIO21            21      /* M.2 pin 9              */
// #define PIN_GPIO22            22      /* M.2 pin 7              */
// #define PIN_GPIO23            23      /* M.2 pin 5              */
// #define PIN_GPIO24            24      /* M.2 pin 3              */
/*  Right side (even pins)                                                    */
// #define PIN_GPIO25            25      /* M.2 pin 8              */
// #define PIN_GPIO26            26      /* M.2 pin 6              */
// #define PIN_GPIO27            27      /* M.2 pin 4              */
// #define PIN_GPIO37            37      /* M.2 pin 34             */
// #define PIN_GPIO38            38      /* M.2 pin 36             */
// #define PIN_GPIO39            39      /* M.2 pin 40             */
// #define PIN_ADC0              40      /* M.2 pin 46 / ADC0      */
// #define PIN_ADC1              41      /* M.2 pin 48 / ADC1      */
// #define PIN_ADC2              42      /* M.2 pin 50 / ADC2      */
// #define PIN_ADC3              43      /* M.2 pin 52 / ADC3      */
// #define PIN_ADC4              44      /* M.2 pin 54 / ADC4      */
// #define PIN_ADC5              45      /* M.2 pin 56 / ADC5      */
/*  CAN bus signals (directly from TCAN1044, no GPIO)                         */
// CAN_P                                /* M.2 pin 28             */
// CAN_N                                /* M.2 pin 30             */

/* -------------------------------------------------------------------------- */
/*  SPI1 instance used by MCP2515                                             */
/* -------------------------------------------------------------------------- */
#define CAN_SPI_INSTANCE spi1
#define CAN_SPI_BAUDRATE (10 * 1000 * 1000) /* 10 MHz               */

/* -------------------------------------------------------------------------- */
/*  I2C0 instance used by EEPROM                                              */
/* -------------------------------------------------------------------------- */
#define EEPROM_I2C_INSTANCE i2c0
#define EEPROM_I2C_ADDR 0x50             /* AT24C256 base address (A0=A1=GND) */
#define EEPROM_I2C_BAUDRATE (400 * 1000) /* 400 kHz             */

/* -------------------------------------------------------------------------- */
/*  Heartbeat LED - PWM configuration                                         */
/* -------------------------------------------------------------------------- */
/*  GPIO36 -> PWM slice 2, channel A (RP2354B: slice = (gpio >> 1) & 0xF)    */
#define HEARTBEAT_PWM_FREQ_HZ 1000
#define HEARTBEAT_FADE_STEP_MS 8

#endif /* CONFIG_H */
